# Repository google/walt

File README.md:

## WALT Latency Timer ##

**DISCLAIMER:** This is not an official Google product.

 * [Post about WALT on Android Developers Blog](http://android-developers.blogspot.ca/2016/04/a-new-method-to-measure-touch-and-audio.html)
 * [Instructional videos showing how to use WALT](https://www.youtube.com/playlist?list=PLd6Fi7WgXfcCEJg1FDqNCoQfpWo7W3J5a)
 * [Detailed usage instructions](docs/usage/WALT_usage.md)
 * Mailing list - [walt-discuss](https://groups.google.com/forum/#!forum/walt-discuss)
 * Low-traffic mailing list for major announcements [walt-announce](https://groups.google.com/forum/#!forum/walt-announce)

WALT is designed to measure the latency of physical sensors and outputs on phones and computers. It can currently perform the following measurements:

 * [Tap latency](docs/TapLatency.md) - time from the moment a finger-like probe touches down (or up) on the screen
   until the kernel timestamps an ACTION_DOWN (or ACTION_UP) event. This physical contact with
   the screen is timed using an accelerometer mounted on the probe.
 * [Drag latency](docs/DragLatency.md) (scroll).
 * [Screen draw latency](docs/ScreenLatency.md) - using a photodiode that detects whether the screen is black or white.
 * [Audio output and microphone latencies](docs/AudioLatency.md).
 * MIDI input and output latencies

The WALT app for Android can be
[installed from Google Play](https://play.google.com/store/apps/details?id=org.kamrik.latency.walt)
or downloaded in the [releases section](https://github.com/google/walt/releases); the iOS app must be built from source.

## Notes
* Hardware build instructions can be found in this repository under `hardware/`.
* Clock synchronization details are described [here](android/WALT/app/src/main/jni/README.md).
* The Android/iOS device and Teensy clocks have a tendency to diverge due to
  differing clock frequencies. This means they will go out of sync after
  several minutes. The workaround is to use the app to re-sync the
  clocks. Some, but not all tests in the app will sync the clocks when starting a measurement.
* Python code used to communicate with WALT from Linux and ChromeOS can be found
  [here](https://chromium.googlesource.com/chromiumos/platform/touchbot/+/master/quickstep/).

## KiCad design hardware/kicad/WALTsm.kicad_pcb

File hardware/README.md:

## Hardware assembly ##
Depending on your specific needs, you may want to introduce some variations.
In most cases it's possible to assemble a device with partial functionality (e.g. only for audio latency) on a solderless breadboard.

### List of suggested parts ###

 * USB OTG cable like
   [this](http://www.amazon.com/Generic-Micro-Cable-Cellphone-Tablet/dp/B00AYPEL56)
   (or a USB Type-C to A adapter)
   for connecting WALT to your phone or tablet
 * Microcontroller board - [Teensy LC](https://www.pjrc.com/teensy/teensyLC.html)
 * Photodiodes - [BPW34](http://www.digikey.com/product-detail/en/osram-opto-semiconductors-inc/BPW34/475-1070-ND/607274) (3 units)
 * Laser - any laser pointer will do, ~1 mW is just fine (5 mW is ok, but avoid stronger ones)
 * Accelerometer board [Adafruit ADXL335](https://www.adafruit.com/product/163) **with filter capacitors removed**.
   It's very important to remove the filter capacitors, otherwise they smooth out the abrupt shock we are looking for.
   Alternatively use the ADXL335 chip directly without the breakout board, but it's rather difficult to solder manually.
 * Some resistors and capacitors - see schematics
 * TRRS connector or wire for audio measurements
 * Clipboard, like [this one](https://upload.wikimedia.org/wikipedia/commons/c/c0/Wood-clipboard.jpg)

### Schematic ###
The current hardware version we use (r0.7) can be found as KiCAD project in this directory.
 * [PDF](WALT_schematic.pdf)
 * Blank PCBs can be ordered directly via [this shared project on OSH Park](https://oshpark.com/shared_projects/M5Z8fYCX)
 * List of parts for version r0.7 - [BOM as a tsv file](WALT_bom_r07.tsv)

### Microcontroller code ###

Important pin numbers from the code listed below, defined in [walt.ino](../arduino/walt/walt.ino)

 * PD_LASER_PIN 14 - Photodiode that looks at the laser
 * G_PIN 15 // Same as A1 - Accelerometer for detecting when touch probe hits the screen
 * PD_SCREEN_PIN 20 // Same as A6 - Photodiode that looks at the screen
 * AUDIO_PIN 22 // Same as A8 - Detects audio signal from headphones output
 * MIC_PIN 23 // Same as A9 - uses PWM to generate a tone for measuring microphone latency.

### Schematic - older version ###
An older version can be found
[here on Upverter](https://upverter.com/kamrik/8af1f3b04e47ab78/WALT_w_audio/)

### More electronics notes ###

 * If using Teensy 3.1 instead of LC, it won’t be able to directly read
   the screen photodiodes - a buffer opamp will be needed. The screen photodiodes
   are bundled as a couple to produce more current, a single photodiode with 1.5M
   resistor should provide the same result, but might be at the limit of what the
   teensy can measure (input impedance), and again, an opamp will be needed.
 * BPW34 photodiode has a small protrusion on the cathode pin (cathode marker).
   Anode has a white dot near it.
 * Note the different setup of the laser and screen photodiode. The laser one
   uses internal pullup resistor (about 20k), enabled by pinMode(PD_LASER_PIN,
   INPUT_PULLUP);

## Mechanical ##

Enclosure must be made from a non conductive and non transparent material.

* The enclosure used for r0.7 production run is available in this repo as [STL](enclosure/WALT_recessed_enclosure.stl) and [STEP](enclosure/WALT_recessed_enclosure.step) files. It also used four M3x6 screws (McMaster-Carr PN 92000A116) and M3 hex nuts (McMaster-Carr PN 91828A211)
* A slightly simpler enclosure suitable for printing on a desktop 3D printer is available as a [public OnShape project](https://cad.onshape.com/documents/6410a1ac7964cb29c4a5ba41/v/32bc78539f48ab7f514eeb31/e/fa513fcc84a825e97020c8b3) and [STL](enclosure/WALT_3DP_enclosure_v7.stl) file
* A minimal enclosure suitable for 2D cutting from any 5 to 8 mm thick substrate is available as a [public OnShape project](https://cad.onshape.com/documents/5d7f21c8877ea8961bc499ef/v/84a66f3baf5f4a8f41be3bd7/e/e2a23559efbeb63be3916123)

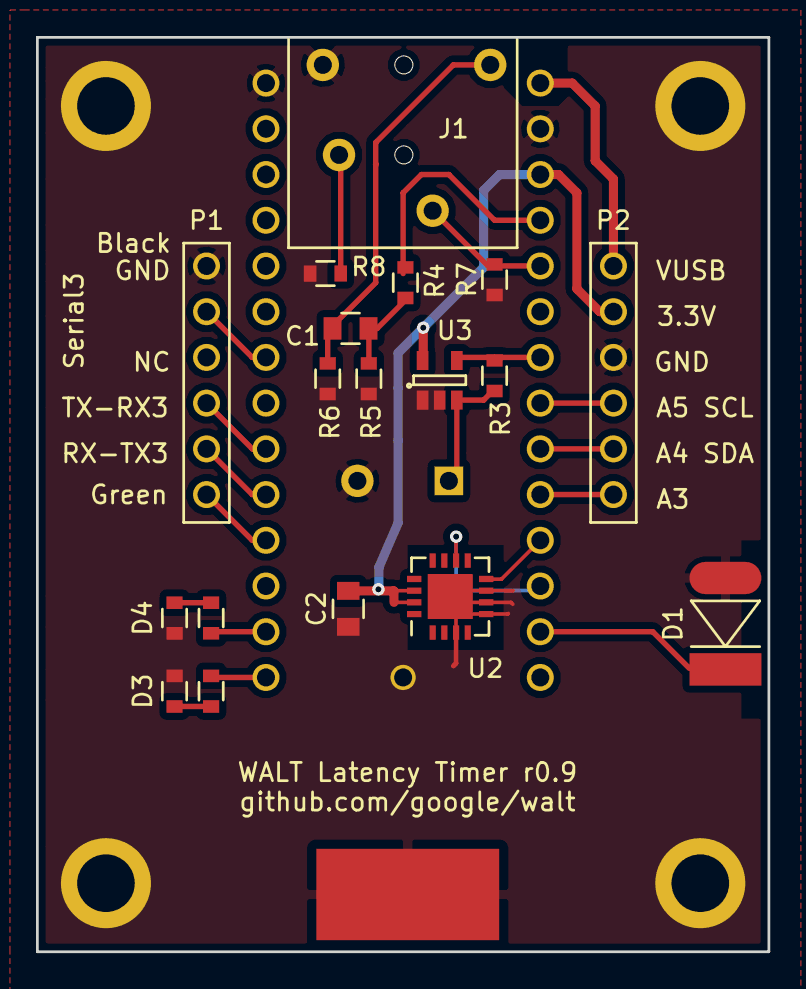
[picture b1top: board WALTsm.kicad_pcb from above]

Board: 2 copper layers, 40.6 x 50.8 mm, 20 parts (1 on the bottom side), 24 nets.

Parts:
C1, C2: 0.1uF; C_0805
D1, D2: Photodiode; BPW34_DIP2
D3, D4: LED; R_0603_pad07mm_long
J1: JACK_TRRS; TRRS_SJ_43514
P1, P2: CONN_01X06; Pin_Header_Straight_1x06
R1, R2: 330; R_0603_pad07mm_long
R3: 510k; R_0603_pad07mm_long
R4: 3,3k; R_0603_pad07mm_long
R5, R7, R8: 100; R_0603_pad07mm_long
R6: 3.3k; R_0603_pad07mm_long
U1: TeensyLC_with_headers; Teensy_DIP-28_W15.24mm
U2: ADXL335; QFN-16-1EP_4x4mm_Pitch0.65mm
U3: LM321MFX; SOT-23-5

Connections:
+3V3: C2.1, P2.5, U1.26, U2.14, U2.15, U3.5
/AUDIO_PIN: J1.3, R7.2, U1.24
/DEBUG_LED1: R2.1, U1.13
/DEBUG_LED2: R1.1, U1.14
/GPIO_A3: P2.1, U1.19
/GPIO_A4: P2.2, U1.20
/GPIO_A5: P2.3, U1.21
/GXY_PIN: U1.17, U2.10
/GZ_PIN: U1.18, U2.8
/MIC_PIN: R4.1, U1.25
/PD_SCREEN_PIN: R3.2, U1.22, U3.4
/SERIAL_CTS: P1.1, U1.11
/SERIAL_RTS: P1.5, U1.7
/SERIAL_RX: P1.3, U1.9
/SERIAL_TX: P1.2, U1.10
/VUSB_5V: P2.6, U1.28
GND: C2.2, D1.2, D2.2, D3.1, D4.1, J1.4, P1.6, P2.4, R5.1, R6.1, R7.1, R8.2, U1.1, U1.27, U2.3, U2.5, U2.6, U2.7, U2.17, U3.1, U3.2
unnamed: C1.1, J1.1, R6.2
unnamed: C1.2, R4.2, R5.2
unnamed: D1.1, U1.16
unnamed: D2.1, R3.1, U3.3
unnamed: D3.2, R1.2
unnamed: D4.2, R2.2
unnamed: J1.2, R8.1

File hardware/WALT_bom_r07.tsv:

Ref	Qty	Description	Type	Package	Manufacturer	Mfg Part #
U3	1	Single Op Amp LM321 (TI, SOT-23)	SMD	SOT-23	Texas Instruments	LM321MFX/NOPB
U2	1	Small, Low Power, 3-Axis 3g Accelerometer	SMD	16-Lead LFCSP_LQ	Analog Devices	ADXL335BCPZ
D3	1	LED GREEN CLEAR 0603 SMD	SMD	0603 (1608 metric), polarized	Lite-On Inc.	LTST-C191KGKT
D4	1	LED RED CLEAR 0603 SMD	SMD	0603 (1608 metric), polarized	Lite-On Inc.	LTST-C191KRKT
C1 C2	2	Capacitor (0.1uF)	SMD	0805 (2012 metric)	Samsung Electro-Mechanics America, Inc.	CL21F104ZBCNNNC
R7,R5	2	Resistor (100) 100 Ohm	SMD	0603 (1608 metric)	Yageo	RC0603FR-07100RL
R4, R6	2	Resistor (3300) 3.3k	SMD	0603 (1608 metric)	Yageo	RC0603JR-073K3L
R3	1	Resistor (510000) 510k	SMD	0603 (1608 metric)	Yageo	RC0603FR-07510KL
R2,R1	2	Resistor (330R) 330 Ohm	SMD	0603 (1608 metric)	Yageo	RC0603JR-07330RL
D1, D2	2	Photodiode	Thru-hole	2-DIP (5.4mm), polarized	Vishay / OSRAM (either)	BPW34
J1	1	Audio jack 3.5 mm, TRRS 4 conductors	Thru-hole	Audio connector, non standard	CUI Inc.	SJ-43514
HEADERS4U1	2	Female headers 2.54mm, 14 pins	Thru-hole		Generic	Generic
P1	1	Male straight headers 2.54mm, 6 pins	Thru-hole		Generic	Generic

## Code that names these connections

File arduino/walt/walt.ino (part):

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
// LEDs
#define LED_PIN_INT 13 // Built-in LED
#define DEBUG_LED1 11  // On r0.7 PCB: D4 - Red
#define DEBUG_LED2 12  // On r0.7 PCB: D3 - Green

// WALT sensors
#define PD_LASER_PIN 14
#define PD_SCREEN_PIN 20  // Same as A6
#define G_PIN 15          // Same as A1
#define GZ_PIN 16         // Same as A2
#define AUDIO_PIN 22      // Same as A8
#define MIC_PIN 23        // Same as A9

// Threshold and hysteresis for screen on/off reading
#define SCREEN_THRESH_HIGH  110
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
void setup() {
    // LEDs
  pinMode(DEBUG_LED1, OUTPUT);
  pinMode(DEBUG_LED2, OUTPUT);
  pinMode(LED_PIN_INT, OUTPUT);

  // Sensors
  pinMode(PD_SCREEN_PIN, INPUT);
  pinMode(G_PIN, INPUT);
  pinMode(GZ_PIN, INPUT);
  pinMode(PD_LASER_PIN, INPUT_PULLUP);
  attachInterrupt(PD_LASER_PIN, irq_laser, CHANGE);

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  short v;
  digitalWrite(DEBUG_LED1, HIGH);
  for (i = 0; i < 1000; i++) {
    v = analogRead(PD_SCREEN_PIN);
    t = time_us;
    send(t);
    send(' ');
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  int v;
  digitalWrite(DEBUG_LED1, HIGH);
  for (i = 0; i < 4000; i++) {
    v = analogRead(GZ_PIN);
    t = time_us;
    send(t);
    send(' ');
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    send_ack(CMD_AUDIO);
  } else if (cmd == CMD_BEEP) {
    long beep_time = time_us;
    tone(MIC_PIN, 5000 /* Hz */);
    send(flip_case(cmd));
    send(' ');
    send(beep_time);
    send_line();
  } else if (cmd == CMD_BEEP_STOP) {
    noTone(MIC_PIN);
    send_ack(CMD_BEEP_STOP);
  } else if (cmd == CMD_MIDI) {
    midi.t = 0;
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    usbMIDI.sendNoteOn(60, 99, 1);
    usbMIDI.send_now();
  } else if (cmd == CMD_AUTO_SCREEN_ON) {
    screen.value = analogRead(PD_SCREEN_PIN) > SCREEN_THRESH_HIGH;
    screen.autosend = true;
    screen.probe = true;
    send_ack(CMD_AUTO_SCREEN_ON);
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    send(" G:");
    send(analogRead(G_PIN));
    send(" PD_screen:");
    send(analogRead(PD_SCREEN_PIN));
    send(" PD_laser:");
    send(analogRead(PD_LASER_PIN));
    send_line();
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
  // Probe audio
  if (sound.probe) {
    int v = analogRead(AUDIO_PIN);
    if (v > 20) {
      sound.t = time_us;
      sound.count++;
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
  // Probe screen
  if (screen.probe) {
    int v = analogRead(PD_SCREEN_PIN);
    if ((screen.value == LOW && v > SCREEN_THRESH_HIGH) || (screen.value != LOW && v < SCREEN_THRESH_LOW)) {
      screen.t = time_us;
      screen.count++;
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
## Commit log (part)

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2016-04-04 Initial import
2016-04-04 Add schematic png
2016-04-04 Add photo of drag latency measurement
2016-04-04 Update README.md
    Add links to detailed docs for tap and drag latency
2016-04-05 Add photo of the stylus to TapLatency.md
2016-04-05 Add photo to main README
    #2 - Added a photo of one of the versions of WALT to the main README file
2016-04-05 Update README.md
    Add link to docs/AudioLatency.md
2016-04-05 Rename README to README.md
2016-04-06 Bump version to upload a release with new icon
2016-04-12 Fix typos in README.md
2016-04-13 Add the deltaT icon in SVG format
2016-04-14 Change photo to show OTG cable clearly
2016-04-14 Update README.md
    Actually change the photo
2016-05-11 Fix median computation
    Existing median implementation assumed a given list of samples was sorted, but
    the callers did not sort. Added a sort utility function and sorted the samples
    before each use of the median function.
2016-05-11 Update gradle version
2016-05-11 Bump version numbers to publish to Play store
2016-05-20 Increase target SDK version to 23, implement runtime USB permissions
2016-05-21 Add MIDI send support to arduino code
2016-05-24 Add MIDI receive support to arduino code
2016-05-24 Add support for testing MIDI output latency
2016-05-25 Add link to Teensyduino beta
2016-05-25 Add PID for Serail+Midi mode to device filter
2016-06-03 Ensure only one instance of the main activity exists at once
    This fixes a crash caused by the system starting a second MainActivity
    instance in response to a USB device being connected.
2016-06-06 Ask for permission to access external storage at runtime
2016-06-07 Switch to experimental Gradle plugin
    This allows building the native library from within Android Studio
2016-06-09 Clear ACTION_USB_DEVICE_ATTACHED intent after it is processed
    This stops the app from trying to connect to a missing WALT device after
    it is resumed.
2016-06-09 Handle USB detach events
    Previously, the ClockManager would always return true for isConnected()
    as long as a connection had succeeded at some point. Unplugging the WALT
    would cause strange behavior including crashes because the app thought
    it was still connected.
2016-06-14 Refactor test logic out of MidiFragment and into MidiTest
2016-06-14 Destroy the audio engine and player object when leaving the audio test
    This prevents the associated resources from being leaked and causing
    degraded performance.
2016-06-15 Refactor ClockManager into a singleton
2016-06-15 Remove dependence of the fragments on MainActivity
    This allows the fragments to work with any activity, not just when
    created from MainActivity.
2016-06-20 Implement initial support for automated testing
2016-06-20 Improve how triggers are handled
2016-06-21 Add protocol versioning and version checking
    This ensures that the user will be notified appropriately when a
    breaking change is made to the WALT protocol and an update must be
    performed.
2016-06-22 Fix MIDI input icon
    It doesn't render properly on Android N.
2016-06-22 Add support to AutoRun for writing test data to a csv
2016-06-23 Resolve a race condition between command and startListener
2016-06-28 Check clock drift after each experiment
    For the the warning is only saved as log message. Once we figure out some UI
    for showing the results (like a histogram) the warning should be displayed as
    part of that UI.
2016-07-07 Add automated and repeated MIDI input testing
2016-07-07 Add screen brightness curve recording - Teensy side
2016-07-07 Screen brightness curve measurement - Android side
2016-07-07 Add animated rectangle on drag latency page
2016-07-07 Only start animation when test starts
    Plus some cleanup.
2016-07-14 Add MPAndroidChart library
    Only gradle files changed for now.
    https://github.com/PhilJay/MPAndroidChart
2016-07-14 Add a fragment for a histogram
    For now just a testing harness. Shows when clicking on "About".
2016-07-21 Add link to videos
2016-07-26 Search for Teensy by PID and VID
2016-07-26 Add an option to the UI to reprogram WALT
2016-07-26 Add code for programming the Teensy from the Android device
    Note that this also includes a copy of the WALT firmware.
    A UI will be added in a later commit.
2016-07-26 Refactor USB connection management so the logic is shared
    ClockManager and BootloaderConnection for the programmer are both
    subclasses of Connection.
2016-08-03 Fix build warning in Arduino code
2016-08-03 Add support for testing cold audio output latency
2016-08-03 Add support for cold latency testing to AutoRun
2016-09-19 Add KiCAD schematic files
2016-09-19 Corrected capacitor value in the PNG simplified schematic
2016-09-19 Add hardware BOM file
2016-09-19 Update WALT_bom_r07.tsv
    Fix some TSV violations to, hopefully, make the file look better in GitHub's viewer.
2016-10-13 Add Serial-over-MIDI communication channel.
    WALT commands will also be read from MIDI channel pressure messages, and
    sending a MIDI program change message for program number 1 will change
    WALT responses to be sent via. MIDI system exclusive messages -- rather
    than the USB serial interface (any other program number will disable
    this feature).
2016-10-13 Whitespace formatting.
2016-10-19 Update README.md to include iOS.
2016-10-19 Update iOS project and add app icon.
2016-10-25 Fix iOS synchronisation slip.
2016-10-25 Update iOS project for Xcode 8.1.
2016-10-26 Add vsync timestamp to screen test
2016-11-02 Add photo to hardware/README
2016-11-02 Fix path to jpg
2016-11-02 Change front page photo
2016-11-15 Allow different PIDs for connecting to Teensy
    Looks like the PID for Serial + MIDI mode changed in Teensyduino 1.31
    Changed the Connection class to allow for any PID.
2016-11-15 Fix a printf("%lu") issue
    Was %lud which resulted in a 'd' after the number
2016-11-15 Bump Android app version to 0.1.5 before release
2016-11-15 Log app and protocol version on startup
2016-11-29 Rename onConnect to onAttach
    To hopefully reduce confusion between connecting physically and the later
    action of establishing a logical connection.
2016-11-29 Rename ClockManager to WaltDevice
    The clock manager was named when its primary task was syncing clocks. Now it
    is managing all of communication with the physical WALT device.
2016-12-01 Split the USB stuff out of WaltDevice class
    Next step is to make WaltDevice use WaltUsbConnecton or WaltTcpConnection
2016-12-01 Rename onAttach back to onConnect + cleanup
    After all it is about the logical connection, not only physical
2016-12-01 Add connection state listener interface
2016-12-06 Eliminate onConnect broadcast
    Removed it with an onConnect handler. The broadcast was only available to one
    runnable anyway.
2016-12-08 Basic TCP bridging kind of works
2016-12-16 Add usage doc
2016-12-19 Link to usage doc from the main README
2017-01-03 Some tests work over TCP
    No audio yet.
    Clock sync is still simplified with several ms error.
    Normal USB mode should work as before.
2017-01-11 Bump iOS protocol version.
2017-01-13 Add a way to pause serial to net forwarding
    Allows to then do a better clock sync drift check
2017-01-16 Sync clocks while pausing 2nd thread
    This allows to interrupt the comms and do complicated stuff
2017-01-19 Implement high precision clock sync via TCP bridge
    All time variables in python code are now in seconds. Except some local ones.
2017-01-23 Implement About page
2017-01-23 Improve phrasing in usage doc
2017-01-25 Create settings page to modify reps per test
2017-01-25 Add a line about iptables in pywalt in bridge mode
    By default random connections between ChromeOS and the Android container is
    not allowed. An iptables command is needed to allow connections to a specific
    port. E.g.:
    iptables -A INPUT -p tcp --dport 50007 -j ACCEPT
2017-01-25 Renaming - get rid of m prefixes in screen response fragment
2017-01-26 Report opposite screen transition times separately (black <-> white)
2017-01-30 Make app control media volume, set volume to max
2017-01-31 Allow scrolling the log in audio test
    Fixes #54
2017-01-31 Clean up Audio results in the log
2017-02-01 Polish UI, automatically increase screen brightness
2017-02-02 Rephrase results output for tap latency
2017-02-02 Add README about screen latency
2017-02-02 rename member variables and small linter fixes
2017-02-03 Add example measurements to Audio README
2017-02-03 Update AudioLatency doc
2017-02-03 Bump Android app version to 0.1.6 before release
2017-02-06 Upgrade gradle and dependencies versions
2017-02-07 Change axis label for brightness curve
2017-02-08 Add option to display recorded waveform
2017-02-08 Add link to privacy policy
2017-02-09 Add mailing lists to README.md
2017-02-10 Add links to code in AudioLatency.md
2017-02-10 Address CR comments
2017-02-14 Add links to 3D enclosure designs
2017-02-14 Add pics for docs
2017-02-15 Display live histogram for tap latency
2017-02-16 Draw ScatterChart for drag latency, showing touch and shifted laser events
2017-02-24 Add setting to disable histograms for tap/blink
2017-02-24 Fix number formatting
2017-02-27 Bump Android app version to 0.1.7 before release
2017-02-28 Add a 100 Ohm resistor from TRRS tip to ground
    Address #86
2017-02-28 Add tap latency screenshot
2017-03-01 Update DragLatency.md
    Describe the drag latency calculation with a screenshot.
2017-03-02 Reset laser events count when turning autosend on
    WALT device was sending the timestamp of the last laser transition from before
    turning autosend on. It was already dealt with in
    7ca4b10a1860e2068dab8ac54093dbe1293d72d1 on Android side but there is no need
    to send this timestamp anyway.
2017-03-06 Item to check linearity of screen brightness variation
2017-03-07 Update ChromeOS.md
    Add instructions for downloading the repo tarball directly from GitHub
2017-03-07 Add drag latency instruction to pywalt README
2017-03-09 Add systrace events for audio and midi tests
2017-03-10 Add unit tests
2017-03-10 Make pywalt a python package
2017-03-10 Slightly better argument parsing in pywalt
2017-03-14 Tackle some small todos
2017-03-14 Add app callback trace event for tap
2017-03-27 make reprogramming more user-friendly
2017-03-29 Allow uploading log to URL
2017-03-29 Modify log uploading dialog and add auto-uploading
2017-04-11 Add measurements for Nexus 6P, Pixel and Pixel XL
2017-04-12 Implement fast-path graphics test
2017-04-12 Add systrace usage docs
2017-04-18 Implement end-to-end tapaudio/tapblink tests
2017-04-25 Split the even and odd blinks in screen test
2017-04-25 Adjust to newer blink_test binary
    It doesn't print the flip time any more, only the vsync time.
2017-05-02 Update schematic PDF
2017-05-05 Add links to new videos in WALT_usage.md
2017-05-06 Update DragLatency.md
    Add link to new video
2017-08-27 Adds end-to-end audio latency test to walt.py
2018-07-11 Update Android build script to ndkBuild plugin
2023-11-22 Fix bug parsing test type
2023-11-22 Add latency measurement method from quickstep
2023-11-22 Make drag latency calculation work with stylus
2025-07-14 Upgrade SDK to v36 and gradle to v8
    Fix associated build and runtime errors.

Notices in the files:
arduino/walt/walt.ino:
Copyright (C) 2015 The Android Open Source Project
Licensed under the Apache License, Version 2.0 (the "License");
